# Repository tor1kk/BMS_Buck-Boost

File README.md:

# Battery Management System (BMS) with Buck-Boost Converter

## Brief

This Battery Management System (BMS) with Buck-Boost Converter is designed for lithium battery applications, providing a flexible voltage range of 3-5V. 
It is particularly useful in projects requiring stable 3.3V or 5V outputs. The system includes a charging circuit, protection circuit, and a DC-DC buck-boost converter, 
ensuring consistent voltage, enhanced battery safety, and adaptability for various devices.

## Features

The key components of the module include:

- **Charging Circuit:** Utilizing the [MCP73831](https://ww1.microchip.com/downloads/en/DeviceDoc/MCP73831-Family-Data-Sheet-DS20001984H.pdf),
  this circuit facilitates the selection of charge current via a resistor and incorporates an indicator diode.

- **Protection Circuit:** Protection is ensured by [DW01A](https://hmsemi.com/downfile/DW01A.PDF) and [FS8205A](https://datasheet.lcsc.com/lcsc/2010271837_FUXINSEMI-FS8205A_C908265.pdf).
  The FS8205A connects the battery's negative to the common ground, with DW01A controlling battery operation. The transistor disconnects the battery in cases of discharge, overcharge, short circuit, etc.

- **DC-DC Buck-Boost Converter:** Employing [TPS63020DSJR](https://www.ti.com/lit/ds/symlink/tps63020.pdf?ts=1700141277158&ref_url=https%253A%252F%252Fwww.ti.com%252Fproduct%252FTPS63020),
  this component enables voltage conversion. The goal is to maintain a constant voltage level regardless of the battery charge, acting as a step-up converter when voltage is low and a step-down converter when it's high.

In summary, this module facilitates battery charging, provides protection, and allows for adjustable output voltage.

> Refer to the complete schematic in `BMS_Buck-Boost.pdf`.

## Module Appearance

## Pinouts

- `-B` and `+B` are used to connect the battery.
- `+B`, `+V`, and `GND` are for connecting to the load, with `+B` used for measuring battery voltage.

## Notes

- While using the module during charging and securing the load, certain limitations exist when the level on the `VBUS` line is high. At this point, transistor Q2 (refer to the schematic [here](https://github.com/tor1kk/BMS_Buck-Boost/blob/master/BMS_Buck-Boost.pdf)) doesn't pass the voltage. This is done to optimize battery charge. If you want to use `VBUS` for the DC-DC converter during charging, employ diode `D4` and an additional diode to prevent current from `+VCC_IN` to `+BATT`.

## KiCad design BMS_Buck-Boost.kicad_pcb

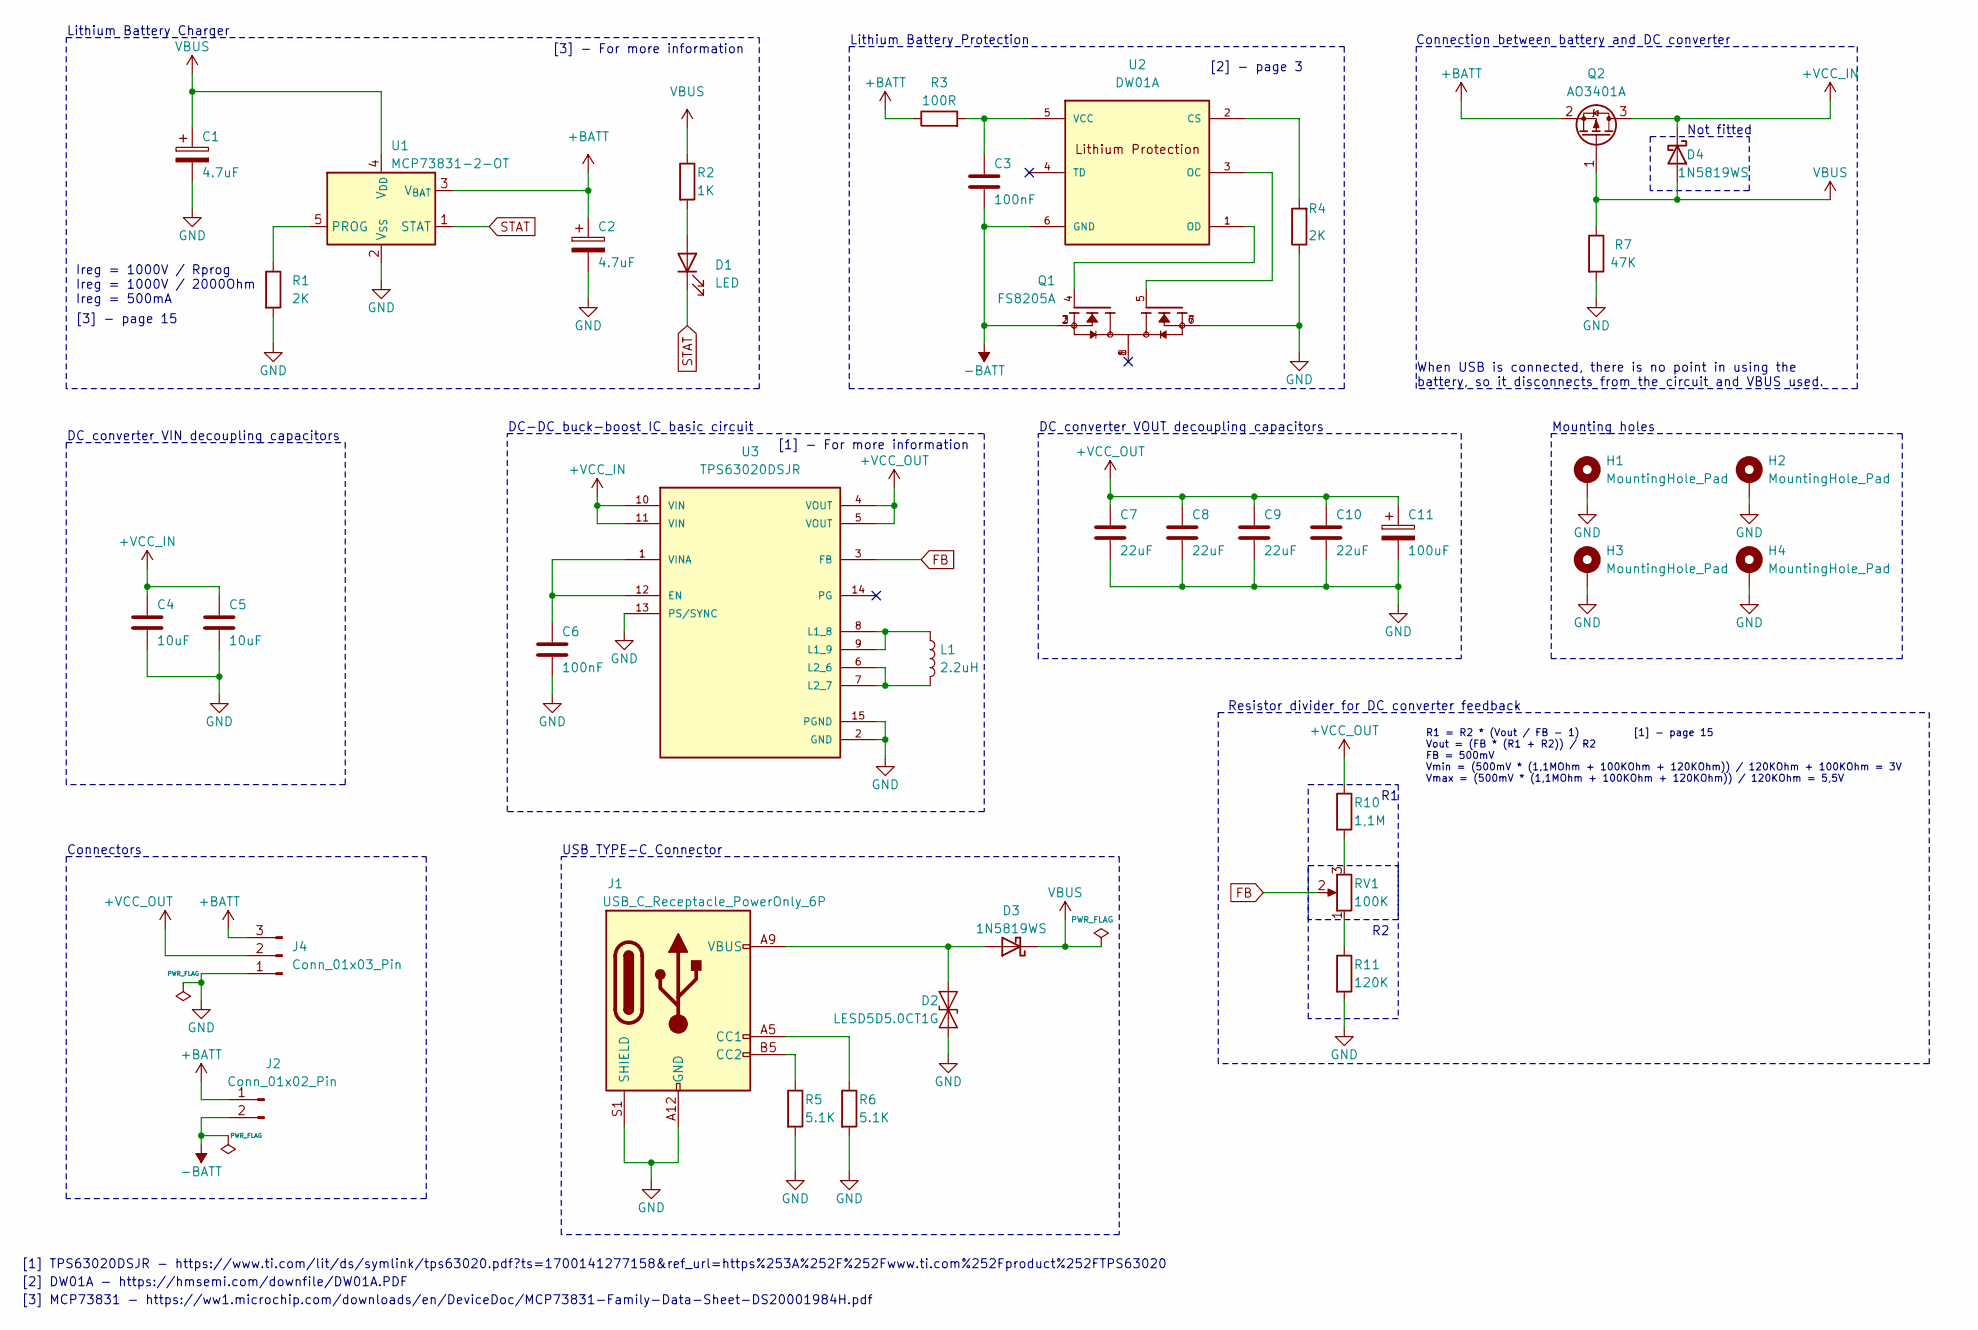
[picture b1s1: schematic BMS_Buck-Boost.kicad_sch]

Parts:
C1, C2: 4.7uF; CP_EIA-3216-18_Kemet-A
C3, C6: 100nF; C_0805_2012Metric
C4, C5: 10uF; C_0805_2012Metric
C7, C8, C9, C10: 22uF; C_0805_2012Metric
C11: 100uF; CP_EIA-3528-21_Kemet-B
D1: LED; D_0805_2012Metric
D2: LESD5D5.0CT1G; D_SOD-523
D3, D4: 1N5819WS; D_SOD-323F
H1, H2, H3, H4: MountingHole_Pad; MountingHole_2.2mm_M2_DIN965_Pad
J1: USB_C_Receptacle_PowerOnly_6P; USB_C_Receptacle_GCT_USB4125-xx-x-0190_6P_TopMnt_Horizontal
J2: Conn_01x02_Pin; PinSocket_1x02_P2.54mm_Vertical
J4: Conn_01x03_Pin; PinHeader_1x03_P2.54mm_Vertical
L1: 2.2uH; L_Chilisin_BMRx00060630
Q1: FS8205A; SOP65P640X120-8N; PARTREV 1.7
Q2: AO3401A; SOT-23
R1, R4: 2K; R_0603_1608Metric
R2: 1K; R_0603_1608Metric
R3: 100R; R_0603_1608Metric
R5, R6: 5.1K; R_0603_1608Metric
R7: 47K; R_0603_1608Metric
R10: 1,1M; R_0603_1608Metric
R11: 120K; R_0603_1608Metric
RV1: 100K; Potentiometer_Bourns_3296W_Vertical
U1: MCP73831-2-OT; SOT-23-5
U2: DW01A; SOT23-6; M_PART_NUMBER DW01A
U3: TPS63020DSJR; IC_TPS63020DSJR

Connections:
+BATT: C2.1, J2.1, J4.3, Q2.2 (S), R3.1, U1.3 (V_{BAT})
+VCC_IN: C4.1, C5.1, D4.1 (K), Q2.3 (D), U3.10 (VIN), U3.11 (VIN)
+VCC_OUT: C7.1, C8.1, C9.1, C10.1, C11.1, J4.2, R10.1, U3.4 (VOUT), U3.5 (VOUT)
-BATT: C3.2, J2.2, Q1.2, Q1.3, U2.6 (GND)
FB: RV1.2, U3.3 (FB)
GND: C1.2, C2.2, C4.2, C5.2, C6.2, C7.2, C8.2, C9.2, C10.2, C11.2, D2.1 (A1), H1.1, H2.1, H3.1, H4.1, J1.A12 (GND), J1.B12 (GND), J1.S1 (SHIELD), J4.1, Q1.6, Q1.7, R1.2, R4.1, R5.2, R6.2, R7.2, R11.2, U1.2 (V_{SS}), U3.2 (GND), U3.13 (PS/SYNC), U3.15 (PGND)
unnamed: D1.2 (A), R2.2
unnamed: D2.2 (A2), D3.2 (A), J1.A9 (VBUS), J1.B9 (VBUS)
unnamed: J1.A5 (CC1), R6.1
unnamed: J1.B5 (CC2), R5.1
unnamed: R10.2, RV1.3
unnamed: R11.1, RV1.1
unnamed: R1.1, U1.5 (PROG)
unnamed: R4.2, U2.2 (CS)
unnamed: Q1.5, U2.3 (OC)
unnamed: Q1.4, U2.1 (OD)
unnamed: C3.1, R3.2, U2.5 (VCC)
unnamed: C6.1, U3.1 (VINA), U3.12 (EN)
unnamed: L1.1, U3.8 (L1_8), U3.9 (L1_9)
unnamed: L1.2, U3.6 (L2_6), U3.7 (L2_7)
STAT: D1.1 (K), U1.1 (STAT)
VBUS: C1.1, D3.1 (K), D4.2 (A), Q2.1 (G), R2.1, R7.1, U1.4 (V_{DD})

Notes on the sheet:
Mounting holes
[3] - For more information
Resistor divider for DC converter feedback
Not fitted
DC-DC buck-boost IC basic circuit
When USB is connected, there is no point in using the battery, so it disconnects from the circuit and VBUS used.
[1] TPS63020DSJR - https://www.ti.com/lit/ds/symlink/tps63020.pdf?ts=1700141277158&ref_url=https%253A%252F%252Fwww.ti.com%252Fproduct%252FTPS63020
Ireg = 1000V / Rprog Ireg = 1000V / 2000Ohm Ireg = 500mA
DC converter VOUT decoupling capacitors
[3] - page 15
R1 = R2 * (Vout / FB - 1) [1] - page 15 Vout = (FB * (R1 + R2)) / R2 FB = 500mV Vmin = (500mV * (1,1MOhm + 100KOhm + 120KOhm)) / 120KOhm + 100KOhm = 3V Vmax = (500mV * (1,1MOhm + 100KOhm + 120KOhm)) / 120KOhm = 5,5V
Connectors
[1] - For more information
DC converter VIN decoupling capacitors
Lithium Battery Protection
USB TYPE-C Connector
[3] MCP73831 - https://ww1.microchip.com/downloads/en/DeviceDoc/MCP73831-Family-Data-Sheet-DS20001984H.pdf
Lithium Battery Charger
[2] DW01A - https://hmsemi.com/downfile/DW01A.PDF
Connection between battery and DC converter
[2] - page 3

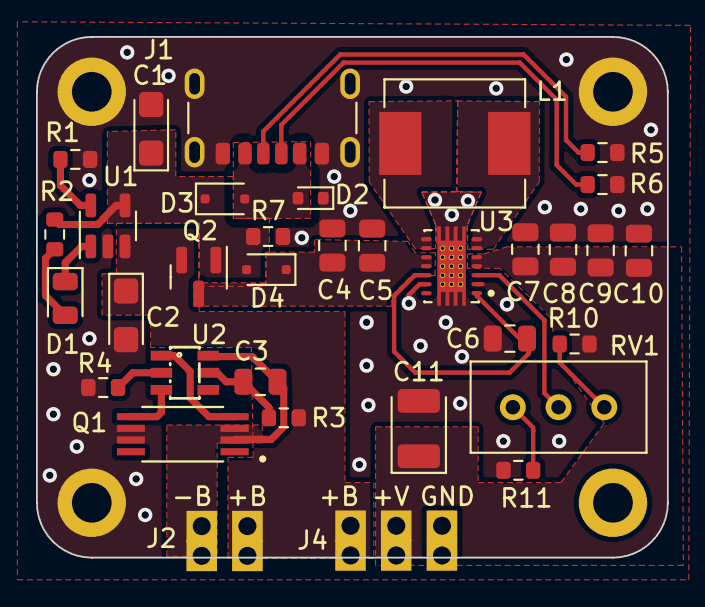
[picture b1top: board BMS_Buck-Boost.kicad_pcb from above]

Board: 2 copper layers, 35.1 x 28.9 mm, 38 parts (0 on the bottom side), 22 nets.

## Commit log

2023-12-30 Create LICENSE
